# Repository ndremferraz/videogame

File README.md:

# Video Game Project (Finished🏁)
The purpose of this repository is to document my process of creating a handheld video game console. My intention with this project is to practice some skills realted to embedded software and electronics while I do something fun.

The Project used a Raspberry Pi Pico to connect to control a OLED screen equiped with a SSD1306 chip using I2C protocol, inputs were read from the a Joystick and 4 different buttons.

In this Project I not only wrote the code using the C/C++ SDK but also designed a PCB for the Circuit. 

The Code can be found under the videogame subfolder and Schematics and PCB found under PacmanProject(Which was the original Idea)

For the creating of the ssd1306.c file I did base myself on the ssd1306 example provided by the raspberry pi foundation, the rest is all mine.

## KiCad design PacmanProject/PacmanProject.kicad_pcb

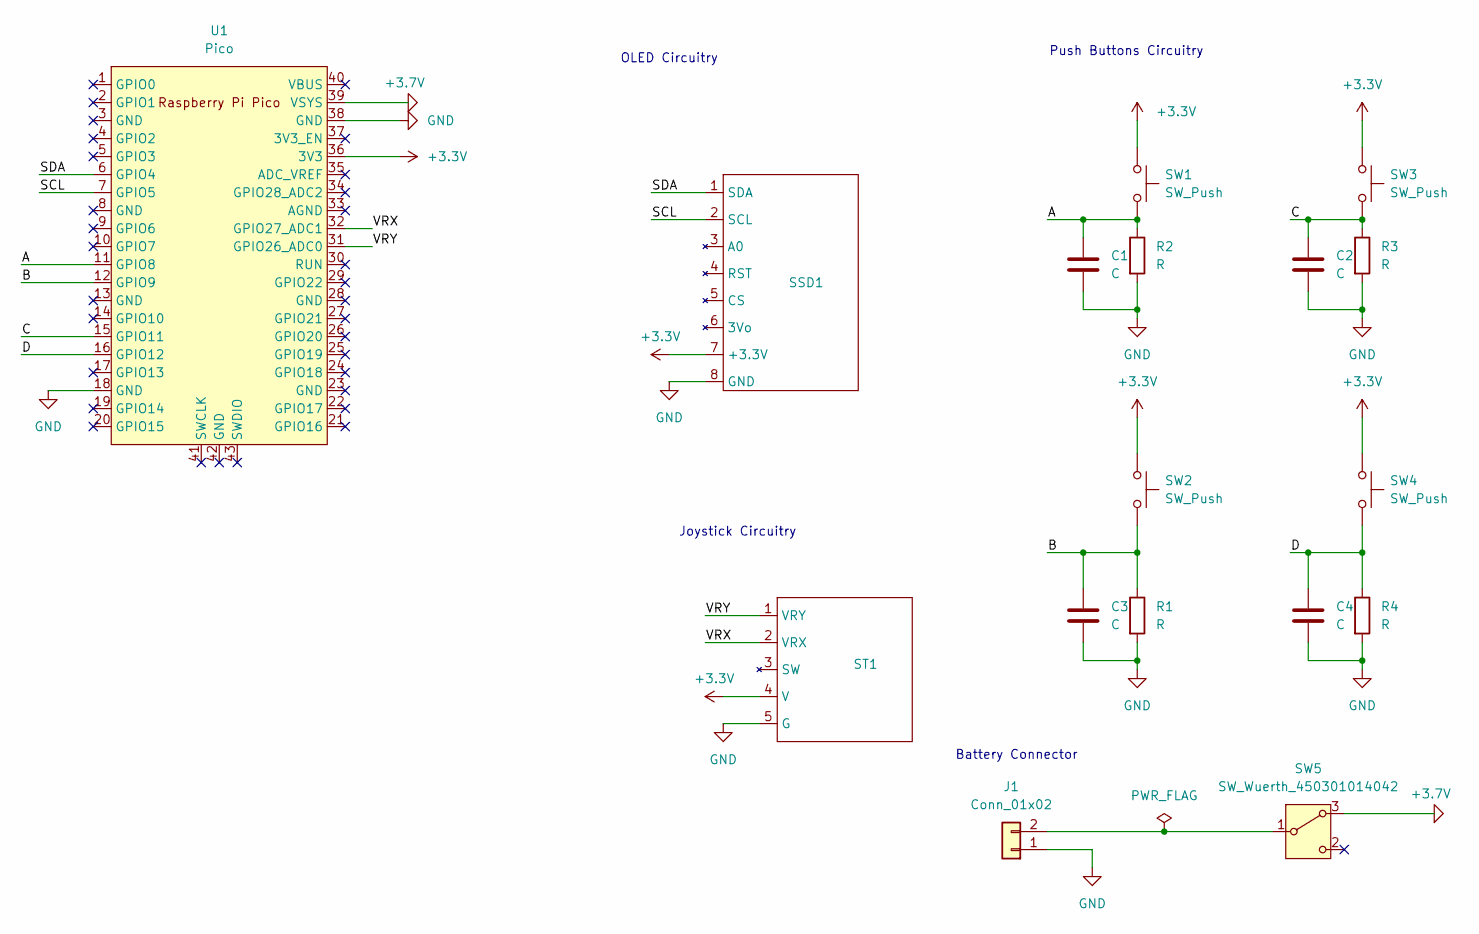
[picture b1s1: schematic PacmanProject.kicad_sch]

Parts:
C1, C2, C3, C4: C; C_Disc_D4.7mm_W2.5mm_P5.00mm
J1: Conn_01x02; JST_PH_S2B-PH-K_1x02_P2.00mm_Horizontal
R1, R2, R3, R4: R; R_Axial_DIN0309_L9.0mm_D3.2mm_P12.70mm_Horizontal
SSD1: Screen
ST1: joystickV2
SW1, SW2, SW3, SW4: SW_Push; SW_PUSH-12mm_Wuerth-430476085716
SW5: SW_Wuerth_450301014042; SW_Slide-03_Wuerth-WS-SLTV_10x2.5x6.4_P2.54mm
U1: Pico; RPi_Pico_SMD_TH

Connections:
+3.3V: SSD1.7 (+3.3V), ST1.4 (V), SW1.1, SW2.1, SW3.1, SW4.1, U1.36 (3V3)
+3.7V: SW5.3 (A), U1.39 (VSYS)
/A: C1.1, R2.1, SW1.2, U1.11 (GPIO8)
/B: C3.1, R1.1, SW2.2, U1.12 (GPIO9)
/C: C2.1, R3.1, SW3.2, U1.15 (GPIO11)
/D: C4.1, R4.1, SW4.2, U1.16 (GPIO12)
/SCL: SSD1.2 (SCL), U1.7 (GPIO5)
/SDA: SSD1.1 (SDA), U1.6 (GPIO4)
/VRX: ST1.2 (VRX), U1.32 (GPIO27_ADC1)
/VRY: ST1.1 (VRY), U1.31 (GPIO26_ADC0)
GND: C1.2, C2.2, C3.2, C4.2, J1.1, R1.2, R2.2, R3.2, R4.2, SSD1.8 (GND), ST1.5 (G), U1.18 (GND), U1.38 (GND)
unnamed: J1.2, SW5.1 (B)

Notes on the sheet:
Push Buttons Circuitry
Joystick Circuitry
OLED Circuitry
Battery Connector

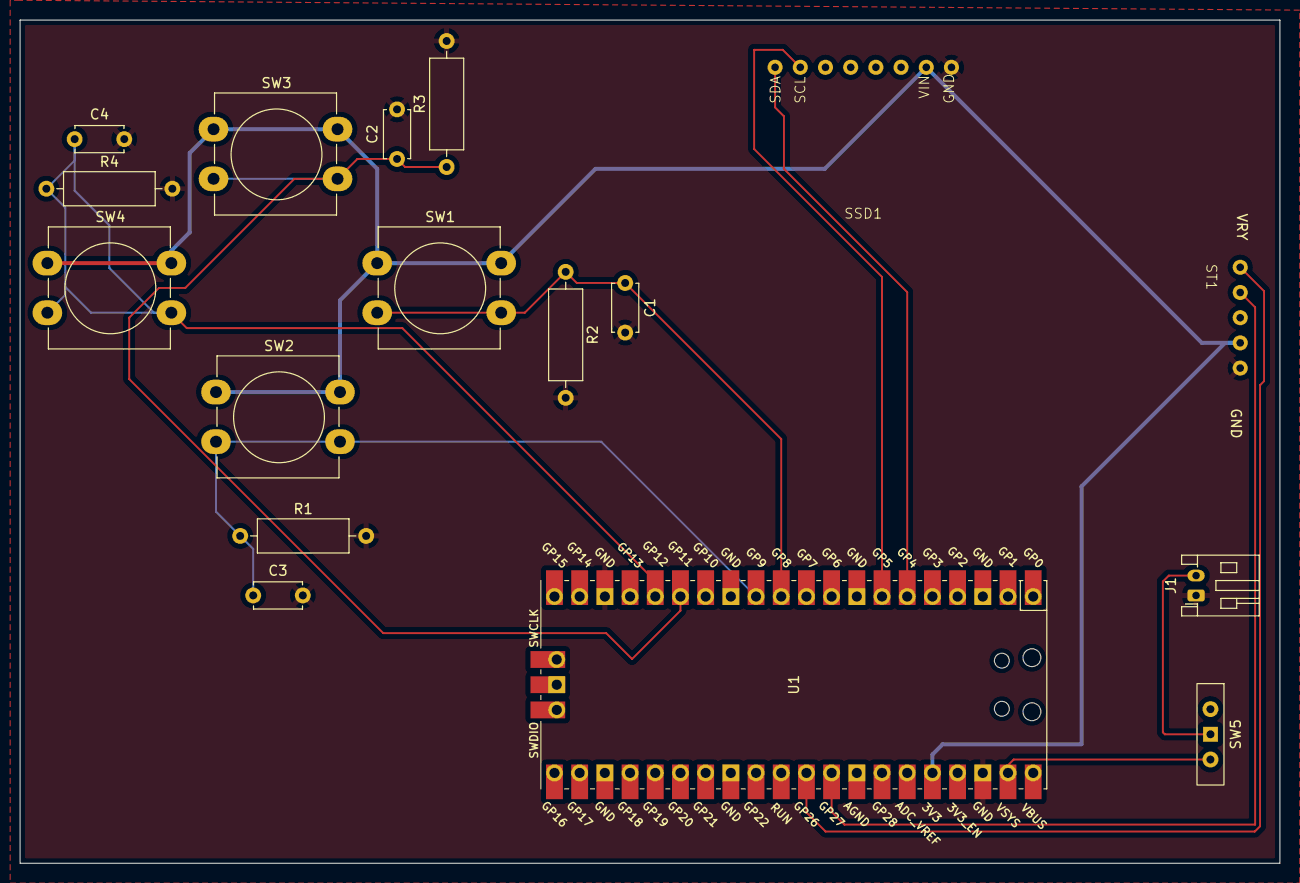
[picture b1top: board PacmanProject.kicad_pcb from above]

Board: 2 copper layers, 127.0 x 85.0 mm, 17 parts (0 on the bottom side), 12 nets.

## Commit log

2025-01-27 Generated project
2025-01-27 GPIO added
2025-01-28 Buttons implemented
2025-01-31 i2c detection implemented
2025-01-31 i2c address found
2025-02-08 added player dynamics
2025-02-08 added enemy, need enemy_move()
2025-02-08 enemy move function added
2025-02-11 shooting functionality added
2025-02-11 header file added
2025-02-12 header file update
2025-02-12 ssd1306.c added
2025-02-12 ssd1306.c and CMake file update to used library properly
2025-02-12 added functions to add characters to image
2025-02-12 fixed the characters for vertical byte scheme and display them statically
2025-02-12 Characters can now be display and move in the display but the movement scheme is wrong
2025-02-12 Updated game functions to new allignment and moved them to another file
2025-02-13 Fixed the uint8_t overflow issue now game is fully functional
2025-02-13 delay increased to avoid crashing
2025-02-24 adding KiCAD files
2025-03-10 Fixed the Connections to display on PCB
2025-03-11 Rename WhatsApp Image 2025-03-10 at 22.49.17_8e483f7c.jpg to Image.jpg
